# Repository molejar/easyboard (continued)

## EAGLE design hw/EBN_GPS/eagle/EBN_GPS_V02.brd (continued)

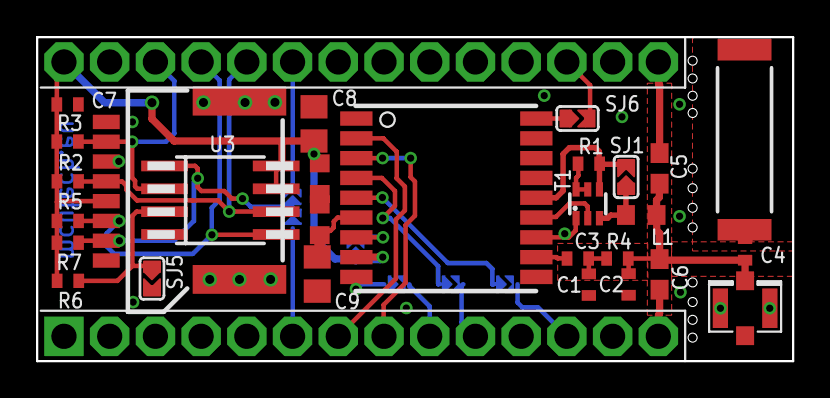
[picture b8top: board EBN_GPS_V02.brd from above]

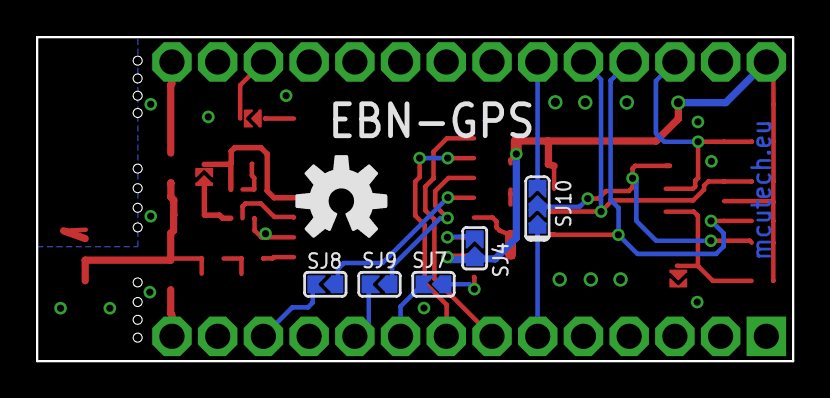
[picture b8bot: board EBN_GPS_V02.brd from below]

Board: 2 copper layers, 42.0 x 18.0 mm, 35 parts (6 on the bottom side), 32 nets.

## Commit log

2019-03-24 Add HW data
2019-04-01 Update description
